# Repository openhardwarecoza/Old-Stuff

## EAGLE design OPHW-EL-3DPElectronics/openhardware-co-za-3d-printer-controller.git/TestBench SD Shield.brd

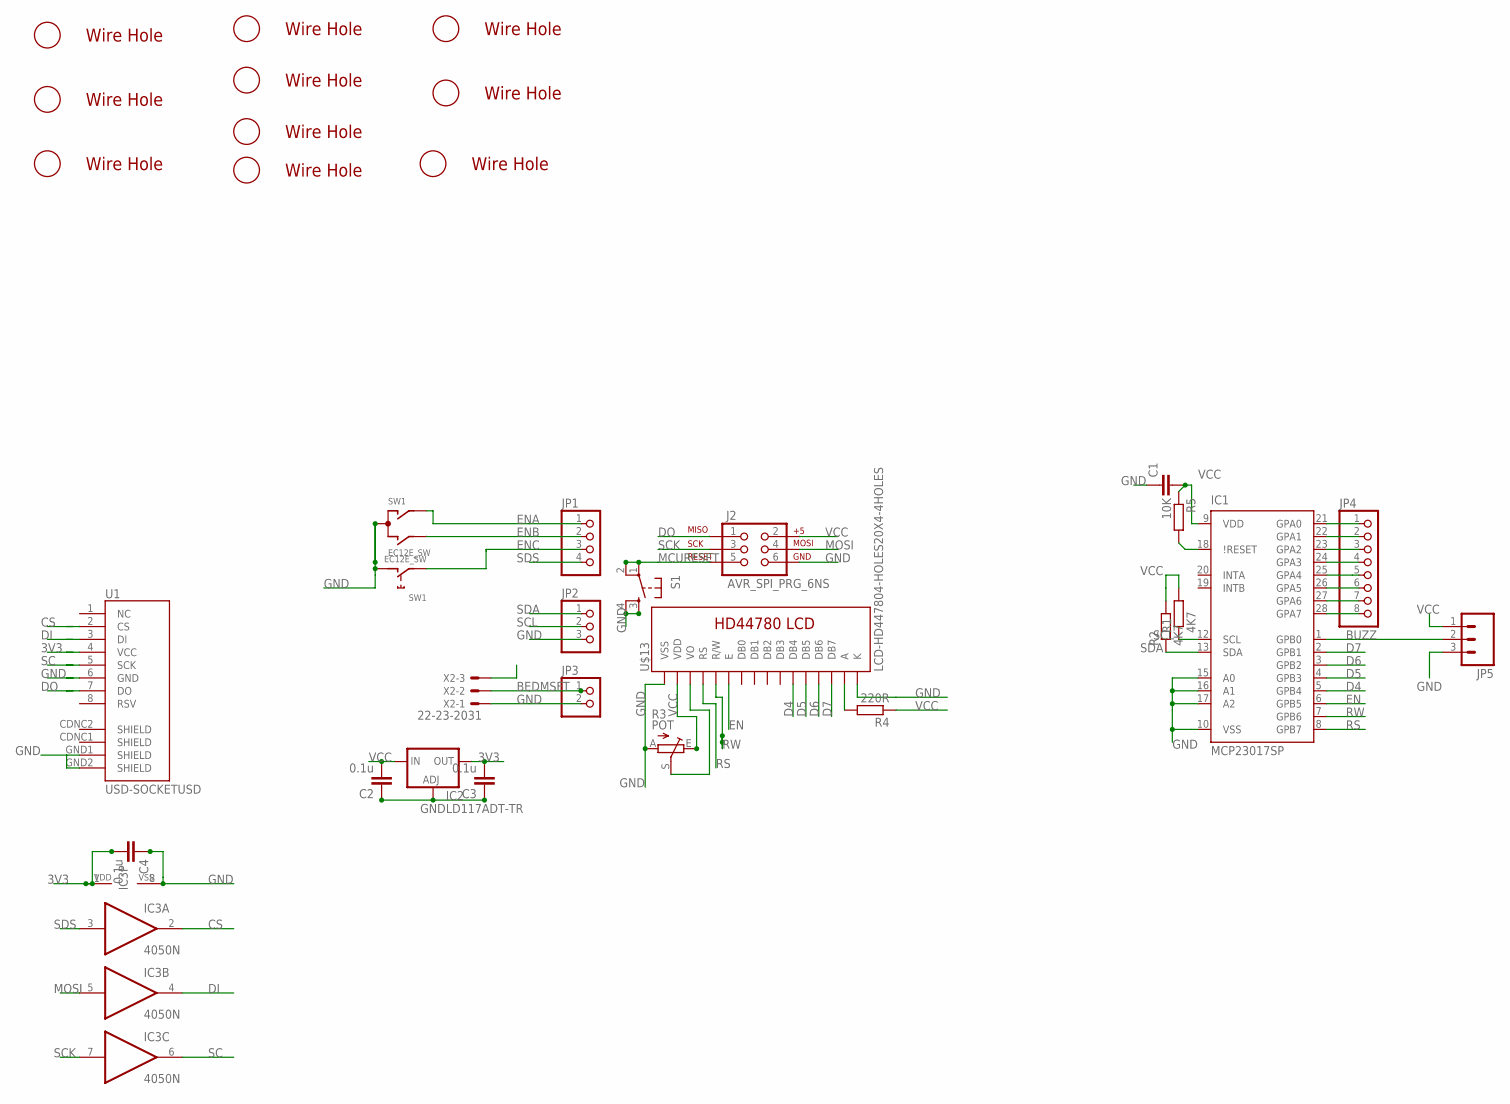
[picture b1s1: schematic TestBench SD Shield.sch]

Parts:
C1: CAPKIT; CAP-PTH-SMALL-KIT
C2, C3, C4: 0.1u; CAP-PTH-SMALL-KIT
IC1: MCP23017SP; DIL28-3
IC2: LD117ADT-TR; DPACK
IC3: 4050N; DIL16
J2: AVR_SPI_PRG_6NS; 2X3-NS
JP1: PINHD-1X4; 1X04
JP2: PINHD-1X3; 1X03
JP3: PINHD-1X2; 1X02
JP4: PINHD-1X8; 1X08
JP5: M03LONGPADS; 1X03_LONGPADS
R1, R2: 4K7; 0204/7
R3: POT; CA9V
R4: 220R; 0204/7
R5: 10K; 0204/7
S1: TAC_SWITCHPTH; TACTILE-PTH
SW1: EC12E_SW; ALPS_EC12E_SW
U1: USD-SOCKETUSD; USD-SOCKET-PP
U$1, U$3, U$5, U$6, U$7, U$8, U$9, U$10, U$11, U$12: 3MMHOLE
U$13: LCD-HD447804-HOLES20X4-4HOLES; LCD-20X4-4HOLES
X2: 22-23-2031

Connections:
3V3: C3.2, C4.2, IC2.4 (OUT), IC3.1 (VDD), U1.4 (VCC)
BEDMSFT: JP3.1, X2.2
BUZZ: IC1.1 (GPB0), JP5.2
CONTRAST: R3.S, U$13.P$3 (VO)
CS: IC3.2 (O), U1.2 (CS)
D4: IC1.5 (GPB4), U$13.P$11 (DB4)
D5: IC1.4 (GPB3), U$13.P$12 (DB5)
D6: IC1.3 (GPB2), U$13.P$13 (DB6)
D7: IC1.2 (GPB1), U$13.P$14 (DB7)
DI: IC3.4 (O), U1.3 (DI)
DO: J2.1, U1.7 (DO)
EN: IC1.6 (GPB5), U$13.P$6 (E)
ENA: JP1.1, SW1.A
ENB: JP1.2, SW1.B
ENC: JP1.3, SW1.E (2)
GND: C1.1, C2.1, C3.1, C4.1, IC1.10 (VSS), IC1.15 (A0), IC1.16 (A1), IC1.17 (A2), IC2.1 (ADJ), IC3.8 (VSS), J2.6, JP2.3, JP3.2, JP5.3, R3.A, S1.3, S1.4, SW1.C, SW1.D (1), U1.6 (GND), U1.GND1 (SHIELD), U1.GND2 (SHIELD), U$13.P$1 (VSS), U$13.P$16 (K), X2.1
MCURESET: J2.5, S1.1, S1.2
MOSI: IC3.5 (I), J2.4
unnamed: IC1.28 (GPA7), JP4.8
unnamed: IC1.27 (GPA6), JP4.7
unnamed: IC1.26 (GPA5), JP4.6
unnamed: IC1.25 (GPA4), JP4.5
unnamed: IC1.24 (GPA3), JP4.4
unnamed: IC1.23 (GPA2), JP4.3
unnamed: IC1.22 (GPA1), JP4.2
unnamed: IC1.21 (GPA0), JP4.1
unnamed: R4.2, U$13.P$15 (A)
unnamed: IC1.18 (\!RESET), R5.2
RS: IC1.8 (GPB7), U$13.P$4 (RS)
RW: IC1.7 (GPB6), U$13.P$5 (R/W)
SC: IC3.6 (O), U1.5 (SCK)
SCK: IC3.7 (I), J2.3
SCL: IC1.12 (SCL), JP2.2, R1.1
SDA: IC1.13 (SDA), JP2.1, R2.1
SDS: IC3.3 (I), JP1.4
VCC: C1.2, C2.2, IC1.9 (VDD), IC2.3 (IN), J2.2, JP5.1, R1.2, R2.2, R3.E, R4.1, R5.1, U$13.P$2 (VDD)

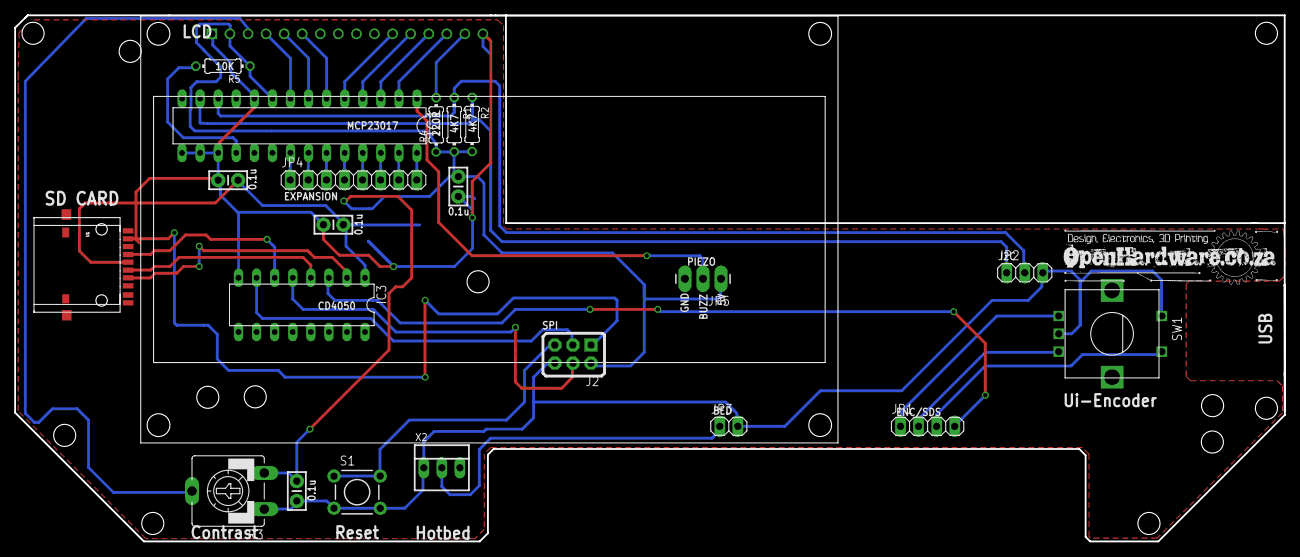
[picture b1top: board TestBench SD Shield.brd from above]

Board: 2 copper layers, 178.5 x 74.0 mm, 35 parts (1 on the bottom side), 36 nets.

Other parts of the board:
U$2, U$4: 3MMHOLE

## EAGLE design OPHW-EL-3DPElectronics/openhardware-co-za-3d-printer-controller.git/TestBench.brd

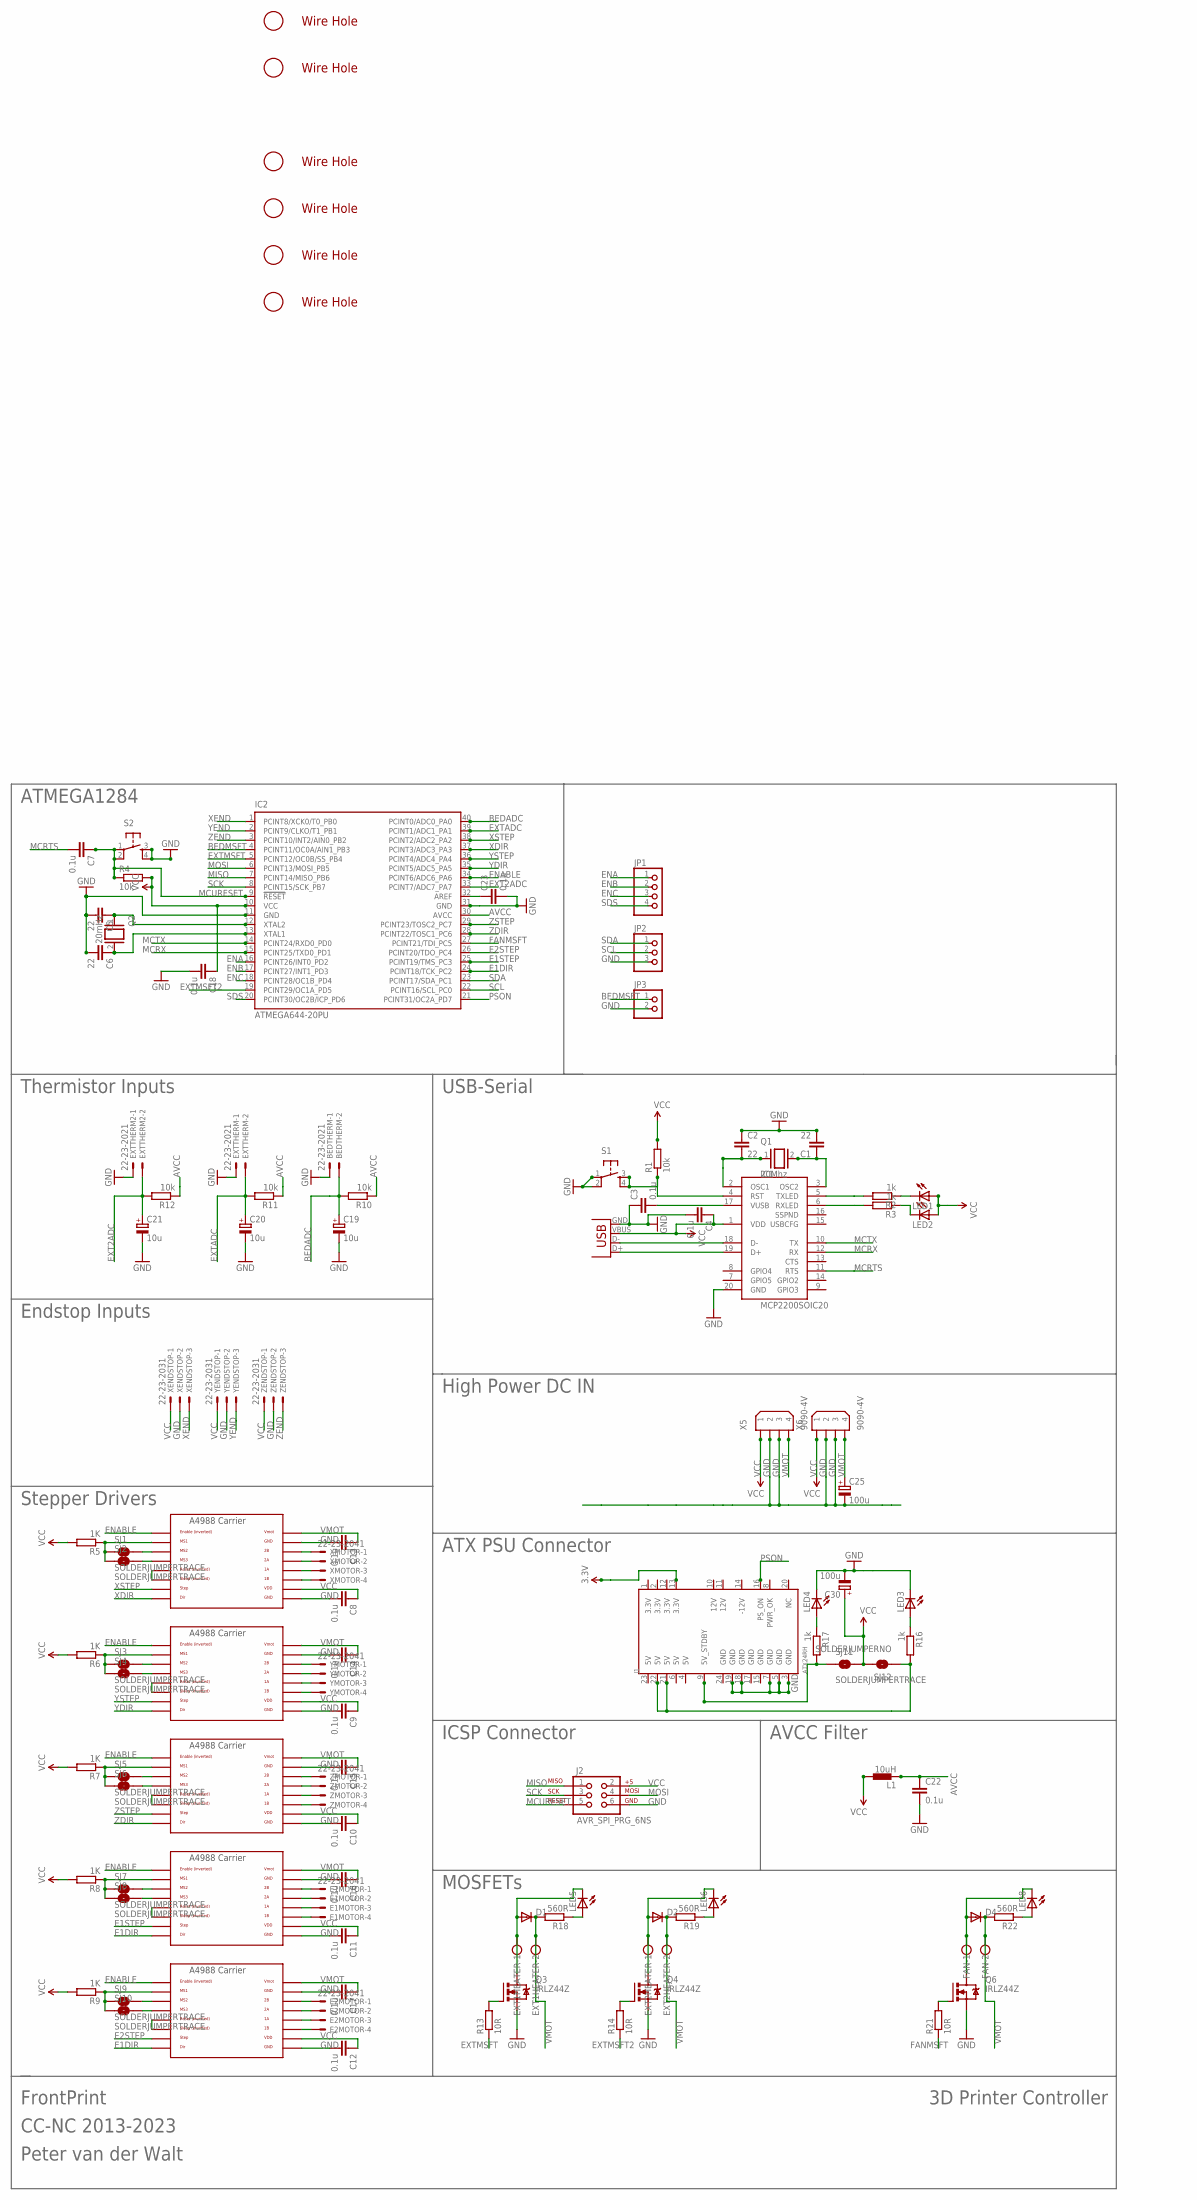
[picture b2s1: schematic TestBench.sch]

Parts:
BEDTHERM: 22-23-2021
C1, C2, C5, C6: 22; CAP-PTH-SMALL-KIT
C3, C4, C7, C8, C9, C10, C11, C12, C13, C14, C15, C16, C17, C18, C22, C23: 0.1u; CAP-PTH-SMALL-KIT
C19, C20, C21: 10u; E2,5-5
C25, C30: 100u; E5-8,5
D1, D2, D4: DIODE1N4148; DIODE-1N4148
E1MOTOR, E2MOTOR: 22-23-2041
EPOLOLU, EPOLOLU2: POLOLU_A4983CARRIER; A4988BREAKOUT
EXT1HEATER, EXT2HEATER: W237-102
EXTTHERM, EXTTHERM2: 22-23-2021
FAN: W237-102
IC1: MCP2200SOIC20; SOIC20
IC2: ATMEGA644-20PU; DIL40
J1: ATX24RH; ATX24_RIGHT_ANGLE
J2: AVR_SPI_PRG_6NS; 2X3-NS
JP1: PINHD-1X4; 1X04
JP2: PINHD-1X3; 1X03
JP3: PINHD-1X2; 1X02
L1: 10uH; BL01RN1A
LED1, LED2, LED3, LED4, LED5, LED6, LED8: LED3MM
Q1: 20Mhz; QS
Q2: 20mHz; QS
Q3, Q4, Q6: IRLZ44Z; TO220BH
R1, R4, R10, R11, R12: 10k; 0204/7
R2, R3, R16, R17: 1k; 0204/7
R5, R6, R7, R8, R9: 1K; 0204/7
R13, R14, R21: 10R; 0204/7
R18, R19, R22: 560R; 0204/7
S1, S2: TAC_SWITCHPTH; TACTILE-PTH
SJ1, SJ2, SJ3, SJ4, SJ5, SJ6, SJ7, SJ8, SJ9, SJ10, SJ11: SOLDERJUMPERTRACE; SJ_2S-TRACE
SJ12: SOLDERJUMPERNO; SJ_2S-NO
U$1, U$3, U$5, U$6, U$7, U$8: 3MMHOLE
X1: USBPTH; USB-B-PTH
X5, X6: 9090-4V
XENDSTOP: 22-23-2031
XMOTOR: 22-23-2041
XPOLOLU: POLOLU_A4983CARRIER; A4988BREAKOUT
YENDSTOP: 22-23-2031
YMOTOR: 22-23-2041
YPOLOLU: POLOLU_A4983CARRIER; A4988BREAKOUT
ZENDSTOP: 22-23-2031
ZMOTOR: 22-23-2041
ZPOLOLU: POLOLU_A4983CARRIER; A4988BREAKOUT

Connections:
3.3V: J1.13 (3.3V)
AVCC: C22.1, IC2.30 (AVCC), L1.1, R10.1, R11.1, R12.1
BEDADC: BEDTHERM.2, C19.+, IC2.40 (PCINT0/ADC0_PA0), R10.2
BEDMSFT: IC2.4 (PCINT11/OC0A/AIN1_PB3), JP3.1
E1DIR: EPOLOLU.DIR, EPOLOLU2.DIR, IC2.24 (PCINT18/TCK_PC2)
E1STEP: EPOLOLU.STEP, IC2.25 (PCINT19/TMS_PC3)
E2STEP: EPOLOLU2.STEP, IC2.26 (PCINT20/TDO_PC4)
ENA: IC2.16 (PCINT26/INT0_PD2), JP1.1
ENABLE: EPOLOLU.EN, EPOLOLU2.EN, IC2.34 (PCINT6/ADC6_PA6), XPOLOLU.EN, YPOLOLU.EN, ZPOLOLU.EN
ENB: IC2.17 (PCINT27/INT1_PD3), JP1.2
ENC: IC2.18 (PCINT28/OC1B_PD4), JP1.3
EXT2ADC: C21.+, EXTTHERM2.2, IC2.33 (PCINT7/ADC7_PA7), R12.2
EXTADC: C20.+, EXTTHERM.2, IC2.39 (PCINT1/ADC1_PA1), R11.2
EXTMSFT: IC2.5 (PCINT12/OC0B/SS_PB4), R13.1
EXTMSFT2: IC2.19 (PCINT29/OC1A_PD5), R14.1
FANMSFT: IC2.27 (PCINT21/TDI_PC5), R21.1
GND: BEDTHERM.1, C1.2, C2.1, C3.1, C4.2, C5.2, C6.2, C8.2, C9.2, C10.2, C11.2, C12.2, C13.2, C14.2, C15.2, C16.2, C17.2, C18.2, C19.-, C20.-, C21.-, C22.2, C23.2, C25.-, C30.-, EPOLOLU.GND, EPOLOLU.GND@0 (GND), EPOLOLU2.GND, EPOLOLU2.GND@0 (GND), EXTTHERM.1, EXTTHERM2.1, IC1.20 (GND), IC2.11 (GND), IC2.31 (GND), J1.3 (GND), J1.5 (GND), J1.7 (GND), J1.18 (GND), J1.19 (GND), J2.6, JP2.3, JP3.2, LED3.K (C), LED4.K (C), Q3.S, Q4.S, Q6.S, S1.1, S1.2, S2.3, S2.4, X1.GND, X5.2, X5.3, X6.2, X6.3, XENDSTOP.2, XPOLOLU.GND, XPOLOLU.GND@0 (GND), YENDSTOP.2, YPOLOLU.GND, YPOLOLU.GND@0 (GND), ZENDSTOP.2, ZPOLOLU.GND, ZPOLOLU.GND@0 (GND)
MCRTS: C7.2, IC1.11 (RTS)
MCRX: IC1.12 (RX), IC2.15 (PCINT25/TXD0_PD1)
MCTX: IC1.10 (TX), IC2.14 (PCINT24/RXD0_PD0)
MCURESET: C7.1, IC2.9 (!RESET), J2.5, R4.1, S2.1, S2.2
MISO: IC2.7 (PCINT14/MISO_PB6), J2.1
MOSI: IC2.6 (PCINT13/MOSI_PB5), J2.4
unnamed: C2.2, IC1.2 (OSC1), Q1.1
unnamed: C1.1, IC1.3 (OSC2), Q1.2
unnamed: IC1.5 (TXLED), R2.2
unnamed: IC1.18 (D-), X1.D-
unnamed: IC1.19 (D+), X1.D+
unnamed: IC1.6 (RXLED), R3.2
unnamed: C3.2, IC1.17 (VUSB)
unnamed: Q3.G, R13.2
unnamed: LED1.K (C), R2.1
unnamed: LED2.K (C), R3.1
unnamed: C5.1, IC2.12 (XTAL2), Q2.1
unnamed: C6.1, IC2.13 (XTAL1), Q2.2
unnamed: IC1.4 (RST), R1.1, S1.3, S1.4
unnamed: R7.1, SJ5.1, SJ6.1, ZPOLOLU.MS1
unnamed: SJ6.2, ZPOLOLU.MS3
unnamed: SJ5.2, ZPOLOLU.MS2
unnamed: EPOLOLU.MS2, SJ7.2
unnamed: EPOLOLU.MS3, SJ8.2
unnamed: EPOLOLU.MS1, R8.1, SJ7.1, SJ8.1
unnamed: SJ3.2, YPOLOLU.MS2
unnamed: SJ4.2, YPOLOLU.MS3
unnamed: R6.1, SJ3.1, SJ4.1, YPOLOLU.MS1
unnamed: SJ1.2, XPOLOLU.MS2
unnamed: SJ2.2, XPOLOLU.MS3
unnamed: R5.1, SJ1.1, SJ2.1, XPOLOLU.MS1
unnamed: XPOLOLU.RST, XPOLOLU.SLP (SLEEP)
unnamed: YPOLOLU.RST, YPOLOLU.SLP (SLEEP)
unnamed: ZPOLOLU.RST, ZPOLOLU.SLP (SLEEP)
unnamed: EPOLOLU.RST, EPOLOLU.SLP (SLEEP)
unnamed: E1MOTOR.1, EPOLOLU.2B
unnamed: E1MOTOR.2, EPOLOLU.2A
unnamed: E1MOTOR.3, EPOLOLU.1A
unnamed: E1MOTOR.4, EPOLOLU.1B
unnamed: ZMOTOR.4, ZPOLOLU.1B
unnamed: ZMOTOR.3, ZPOLOLU.1A
unnamed: ZMOTOR.2, ZPOLOLU.2A
unnamed: ZMOTOR.1, ZPOLOLU.2B
unnamed: YMOTOR.4, YPOLOLU.1B
unnamed: YMOTOR.3, YPOLOLU.1A
unnamed: YMOTOR.2, YPOLOLU.2A
unnamed: YMOTOR.1, YPOLOLU.2B
unnamed: XMOTOR.4, XPOLOLU.1B
unnamed: XMOTOR.3, XPOLOLU.1A
unnamed: XMOTOR.2, XPOLOLU.2A
unnamed: XMOTOR.1, XPOLOLU.2B
unnamed: EPOLOLU2.MS2, SJ9.2
unnamed: EPOLOLU2.MS3, SJ10.2
unnamed: EPOLOLU2.MS1, R9.1, SJ9.1, SJ10.1
unnamed: EPOLOLU2.RST, EPOLOLU2.SLP (SLEEP)
unnamed: E2MOTOR.1, EPOLOLU2.2B
unnamed: E2MOTOR.2, EPOLOLU2.2A
unnamed: E2MOTOR.3, EPOLOLU2.1A
unnamed: E2MOTOR.4, EPOLOLU2.1B
unnamed: C23.1, IC2.32 (AREF)
unnamed: D1.A, EXT1HEATER.1, LED5.K (C), Q3.D
unnamed: Q4.G, R14.2
unnamed: D2.A, EXT2HEATER.1, LED6.K (C), Q4.D
unnamed: J1.21 (5V), J1.22 (5V), R16.2, SJ12.1
unnamed: LED5.A, R18.1
unnamed: J1.9 (5V_STDBY), R17.2, SJ11.1
unnamed: LED4.A, R17.1
unnamed: LED3.A, R16.1
unnamed: Q6.G, R21.2
unnamed: LED6.A, R19.1
unnamed: D4.A, FAN.1, LED8.K (C), Q6.D
unnamed: LED8.A, R22.1
PSON: IC2.21 (PCINT31/OC2A_PD7), J1.16 (PS_ON)
SCK: IC2.8 (PCINT15/SCK_PB7), J2.3
SCL: IC2.22 (PCINT16/SCL_PC0), JP2.2
SDA: IC2.23 (PCINT17/SDA_PC1), JP2.1
SDS: IC2.20 (PCINT30/OC2B/ICP_PD6), JP1.4
VCC: C4.1, C8.1, C9.1, C10.1, C11.1, C12.1, C18.1, C30.+, EPOLOLU.VDD, EPOLOLU2.VDD, IC1.1 (VDD), IC2.10 (VCC), J2.2, L1.2, LED1.A, LED2.A, R1.2, R4.2, R5.2, R6.2, R7.2, R8.2, R9.2, SJ11.2, SJ12.2, X1.VBUS, X5.1, X6.1, XENDSTOP.1, XPOLOLU.VDD, YENDSTOP.1, YPOLOLU.VDD, ZENDSTOP.1, ZPOLOLU.VDD
VMOT: C13.1, C14.1, C15.1, C16.1, C17.1, C25.+, D1.C, D2.C, D4.C, EPOLOLU.VMOT, EPOLOLU2.VMOT, EXT1HEATER.2, EXT2HEATER.2, FAN.2, R18.2, R19.2, R22.2, X5.4, X6.4, XPOLOLU.VMOT, YPOLOLU.VMOT, ZPOLOLU.VMOT
XDIR: IC2.37 (PCINT3/ADC3_PA3), XPOLOLU.DIR
XEND: IC2.1 (PCINT8/XCK0/T0_PB0), XENDSTOP.3
XSTEP: IC2.38 (PCINT2/ADC2_PA2), XPOLOLU.STEP
YDIR: IC2.35 (PCINT5/ADC5_PA5), YPOLOLU.DIR
YEND: IC2.2 (PCINT9/CLKO/T1_PB1), YENDSTOP.3
YSTEP: IC2.36 (PCINT4/ADC4_PA4), YPOLOLU.STEP
ZDIR: IC2.28 (PCINT22/TOSC1_PC6), ZPOLOLU.DIR
ZEND: IC2.3 (PCINT10/INT2/AIN0_PB2), ZENDSTOP.3
ZSTEP: IC2.29 (PCINT23/TOSC2_PC7), ZPOLOLU.STEP

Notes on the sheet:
Thermistor Inputs
Endstop Inputs
Stepper Drivers
USB-Serial
AVCC Filter
ATX PSU Connector
ICSP Connector
MOSFETs
High Power DC IN
ATMEGA1284
FrontPrint
CC-NC 2013-2023
Peter van der Walt
3D Printer Controller

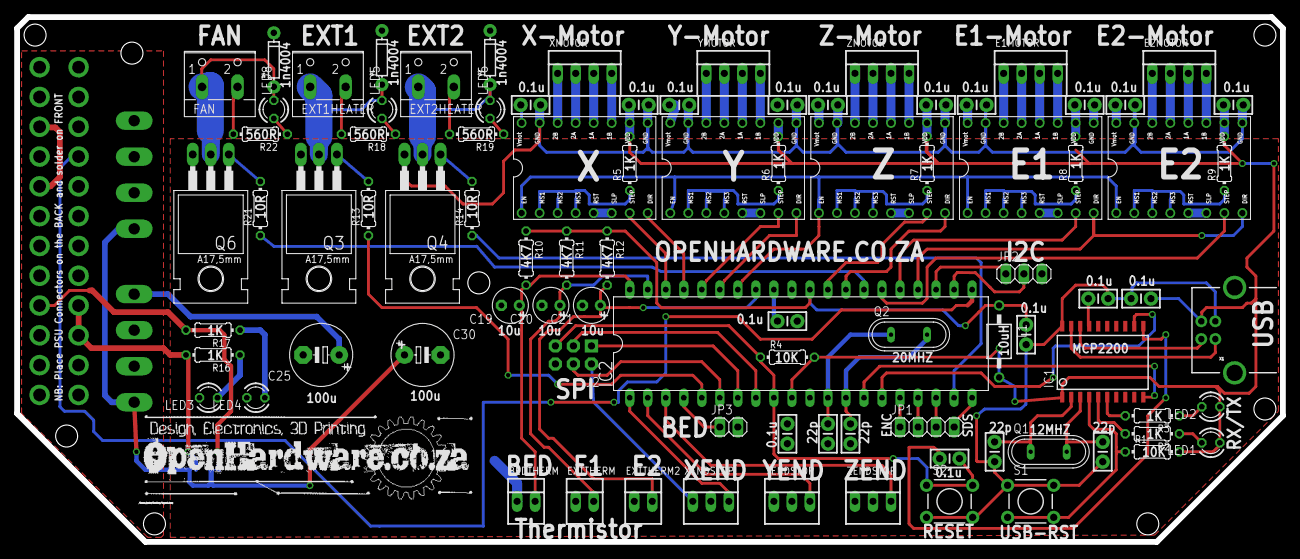
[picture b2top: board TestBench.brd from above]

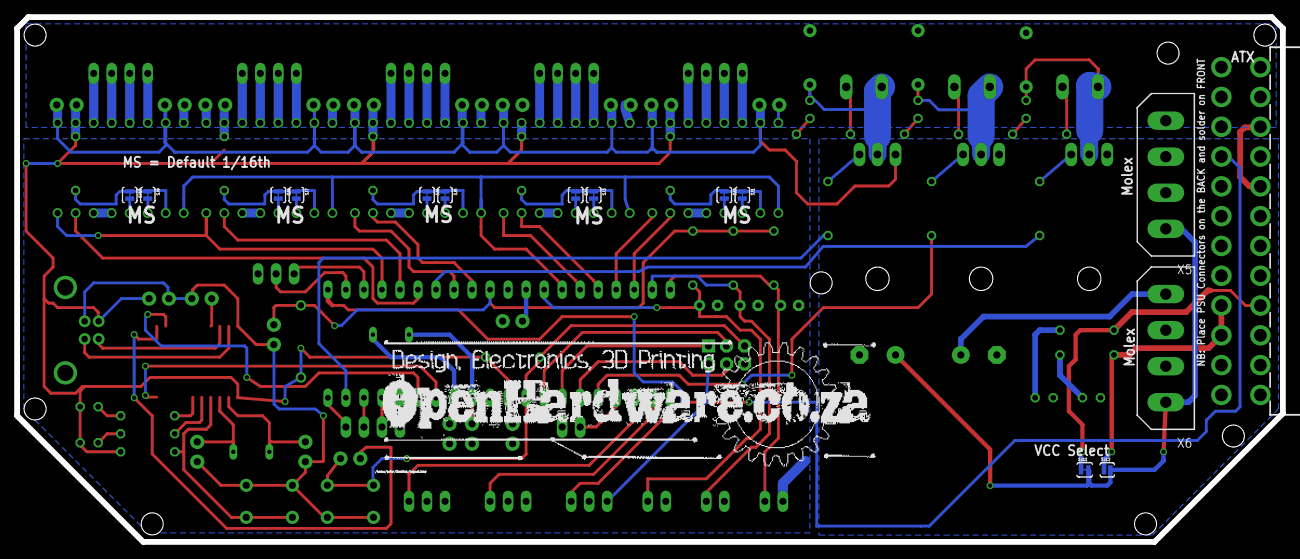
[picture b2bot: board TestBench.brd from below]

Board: 2 copper layers, 178.4 x 74.0 mm, 112 parts (15 on the bottom side), 104 nets.

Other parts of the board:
U$2, U$4: 3MMHOLE

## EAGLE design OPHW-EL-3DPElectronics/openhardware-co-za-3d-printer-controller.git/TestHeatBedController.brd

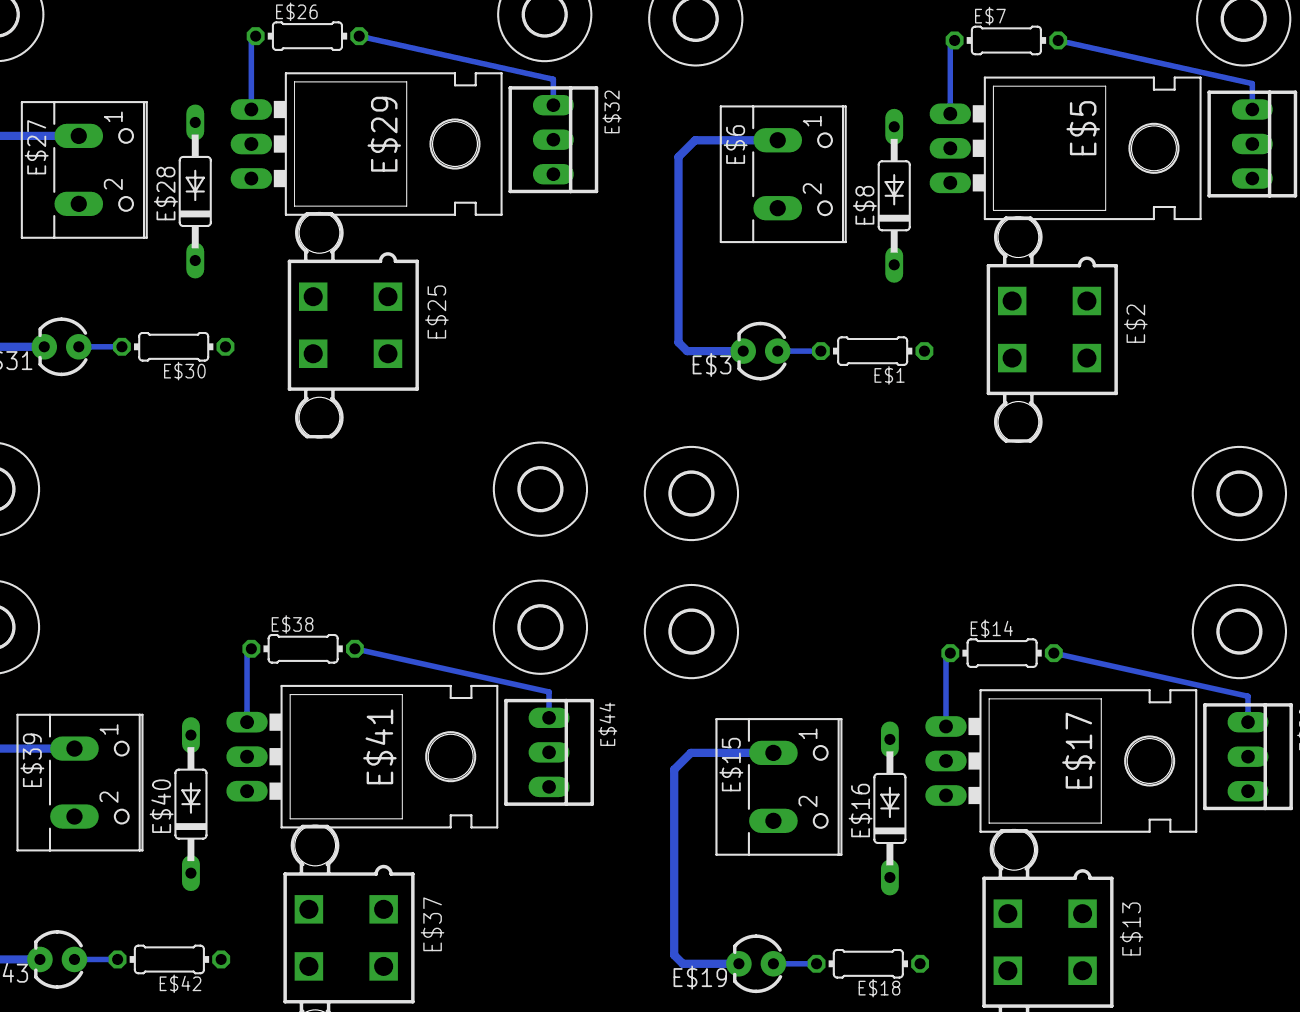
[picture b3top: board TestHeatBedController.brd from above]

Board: 2 copper layers, 48 parts (0 on the bottom side), 24 nets.

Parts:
E$1, E$7, E$14, E$18, E$26, E$30, E$38, E$42: 0204/7
E$2, E$13, E$25, E$37: 5566-4
E$3, E$19, E$31, E$43: LED3MM
E$4, E$20, E$32, E$44: 22-23-2031
E$5, E$17, E$29, E$41: TO-220-ALT
E$6, E$15, E$27, E$39: W237-102
E$8, E$16, E$28, E$40: C2992
E$9, E$10, E$11, E$12, E$21, E$22, E$23, E$24, E$33, E$34, E$35, E$36, E$45, E$46, E$47, E$48: 3,0

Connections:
12V: E$1.1, E$2.3, E$2.4, E$6.2, E$8.C
12V1: E$13.3, E$13.4, E$15.2, E$16.C, E$18.1
12V2: E$25.3, E$25.4, E$27.2, E$28.C, E$30.1
12V3: E$37.3, E$37.4, E$39.2, E$40.C, E$42.1
GATE: E$5.IN, E$7.1
GATE1: E$14.1, E$17.IN
GATE2: E$26.1, E$29.IN
GATE3: E$38.1, E$41.IN
GND: E$2.1, E$2.2, E$4.3, E$5.OUT
GND1: E$13.1, E$13.2, E$17.OUT, E$20.3
GND2: E$25.1, E$25.2, E$29.OUT, E$32.3
GND3: E$37.1, E$37.2, E$41.OUT, E$44.3
S$1: E$18.2, E$19.A
S$2: E$1.2, E$3.A
S$3: E$30.2, E$31.A
S$4: E$42.2, E$43.A
SIG: E$4.1, E$7.2
SIG1: E$14.2, E$20.1
SIG2: E$26.2, E$32.1
SIG3: E$38.2, E$44.1
VMOS: E$3.K, E$4.2, E$5.GND, E$6.1, E$8.A
VMOS1: E$15.1, E$16.A, E$17.GND, E$19.K, E$20.2
VMOS2: E$27.1, E$28.A, E$29.GND, E$31.K, E$32.2
VMOS3: E$39.1, E$40.A, E$41.GND, E$43.K, E$44.2

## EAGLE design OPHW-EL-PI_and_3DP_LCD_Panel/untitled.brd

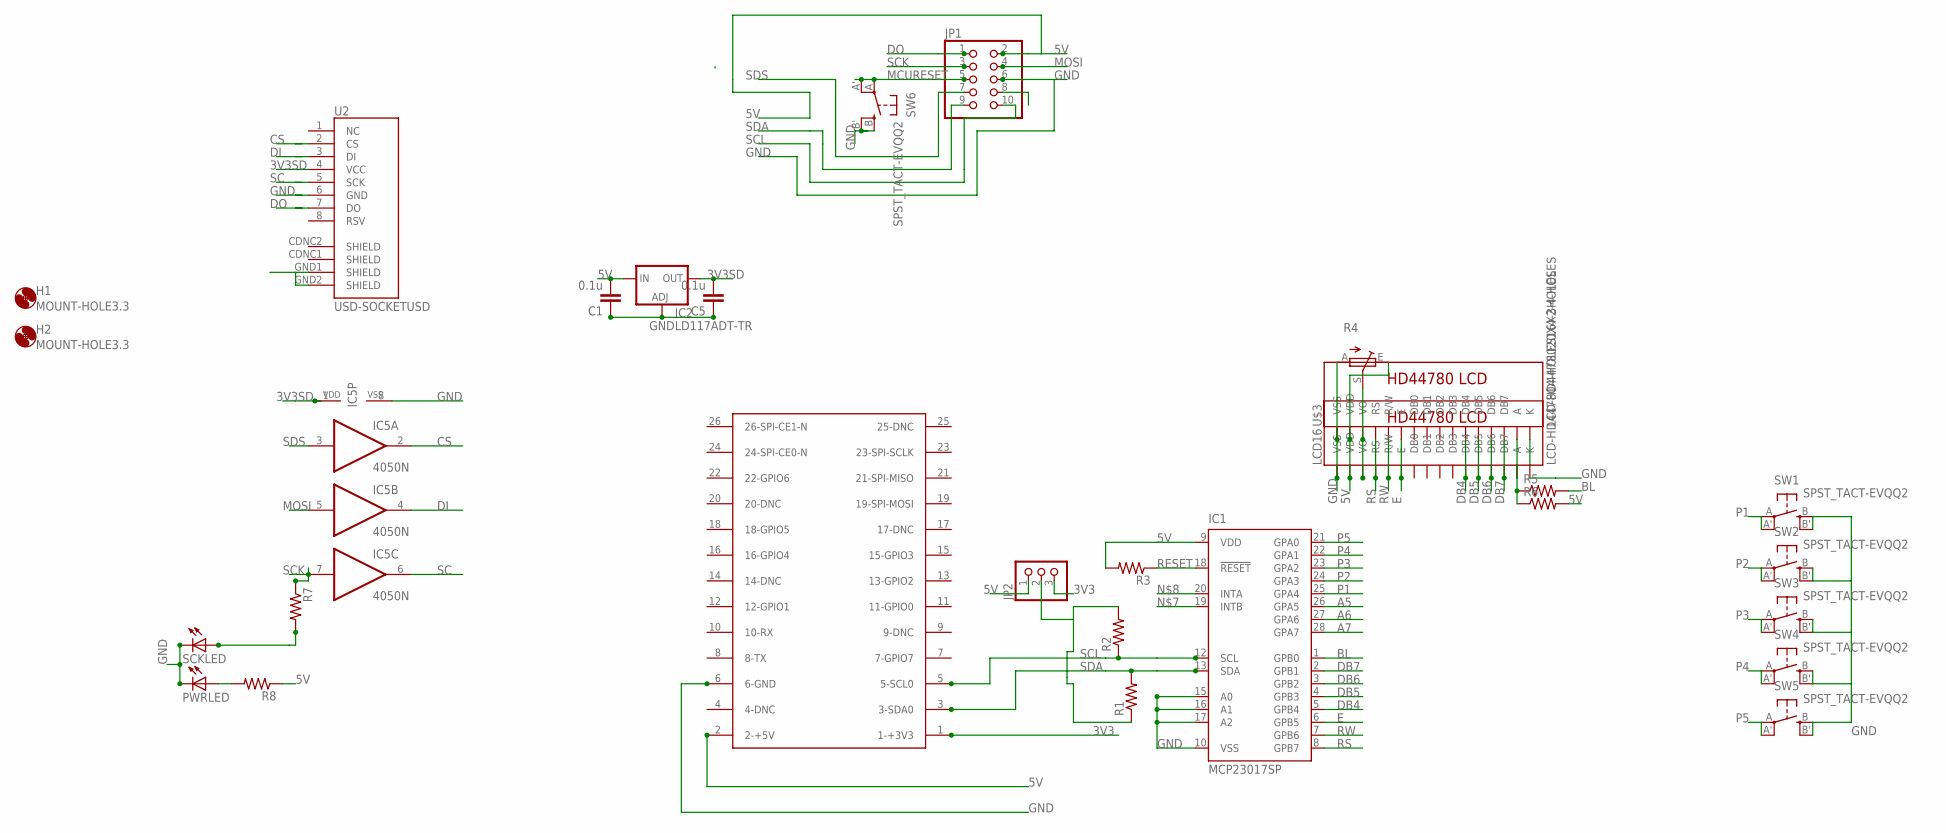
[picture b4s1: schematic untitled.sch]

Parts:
C1, C5: 0.1u; CAP-PTH-SMALL-KIT
H1, H2: MOUNT-HOLE3.3; 3,3
IC1: MCP23017SP; DIL28-3
IC2: LD117ADT-TR; DPACK
IC5: 4050N; DIL16
JP1: PINHD-2X5; 2X05
JP2: PINHD-1X3; 1X03
LCD16: LCD-HD447804-HOLES16X2-4-HOLES; LCD-16X2-4HOLES
PWRLED: LED1206; LED-1206
R1, R2, R3, R5, R6, R7, R8: R-US_0204/7; 0204/7
R4: TRIM_EU-CA6V; CA6V
SCKLED: LED1206; LED-1206
SW1, SW2, SW3, SW4, SW5, SW6: SPST_TACT-EVQQ2; EVQ-Q2
U2: USD-SOCKETUSD; USD-SOCKET-PP
U$2: RASPBERRY-PI
U$3: LCD-HD4478020X4-3HOLES; LCD-20X4-3HOLES

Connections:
3V3: JP2.3, U$2.1 (1-+3V3)
3V3SD: C5.2, IC2.4 (OUT), IC5.1 (VDD), U2.4 (VCC)
5V: C1.2, IC1.9 (VDD), IC2.3 (IN), JP1.2, JP2.1, LCD16.2 (VDD), R3.2, R4.E, R6.2, R8.1, U$2.2 (2-+5V), U$3.P$2 (VDD)
A5: IC1.26 (GPA5)
A6: IC1.27 (GPA6)
A7: IC1.28 (GPA7)
BL: IC1.1 (GPB0), R5.2
CS: IC5.2 (O), U2.2 (CS)
DB4: IC1.5 (GPB4), LCD16.11 (DB4), U$3.P$11 (DB4)
DB5: IC1.4 (GPB3), LCD16.12 (DB5), U$3.P$12 (DB5)
DB6: IC1.3 (GPB2), LCD16.13 (DB6), U$3.P$13 (DB6)
DB7: IC1.2 (GPB1), LCD16.14 (DB7), U$3.P$14 (DB7)
DI: IC5.4 (O), U2.3 (DI)
DO: JP1.1, U2.7 (DO)
E: IC1.6 (GPB5), LCD16.6 (E), U$3.P$6 (E)
GND: C1.1, C5.1, IC1.10 (VSS), IC1.15 (A0), IC1.16 (A1), IC1.17 (A2), IC2.1 (ADJ), IC5.8 (VSS), JP1.6, LCD16.1 (VSS), LCD16.16 (K), PWRLED.C, R4.A, SCKLED.C, SW1.B (S), SW1.B' (S1), SW2.B (S), SW2.B' (S1), SW3.B (S), SW3.B' (S1), SW4.B (S), SW4.B' (S1), SW5.B (S), SW5.B' (S1), SW6.B (S), SW6.B' (S1), U2.6 (GND), U2.GND1 (SHIELD), U2.GND2 (SHIELD), U$2.6 (6-GND), U$3.P$1 (VSS)
I2CPULL: JP2.2, R1.1, R2.2
MCURESET: JP1.5, SW6.A, SW6.A' (P1)
MOSI: IC5.5 (I), JP1.4
unnamed: LCD16.3 (VO), R4.S, U$3.P$3 (VO)
unnamed: LCD16.15 (A), R5.1, R6.1, U$3.P$15 (A)
unnamed: PWRLED.A, R8.2
unnamed: R7.2, SCKLED.A
P1: IC1.25 (GPA4), SW1.A, SW1.A' (P1)
P2: IC1.24 (GPA3), SW2.A, SW2.A' (P1)
P3: IC1.23 (GPA2), SW3.A, SW3.A' (P1)
P4: IC1.22 (GPA1), SW4.A, SW4.A' (P1)
P5: IC1.21 (GPA0), SW5.A, SW5.A' (P1)
RESET: IC1.18 (!RESET), R3.1
RS: IC1.8 (GPB7), LCD16.4 (RS), U$3.P$4 (RS)
RW: IC1.7 (GPB6), LCD16.5 (R/W), U$3.P$5 (R/W)
SC: IC5.6 (O), U2.5 (SCK)
SCK: IC5.7 (I), JP1.3, R7.1
SCL: IC1.12 (SCL), JP1.10, R2.1, U$2.5 (5-SCL0)
SDA: IC1.13 (SDA), JP1.9, R1.2, U$2.3 (3-SDA0)
SDS: IC5.3 (I), JP1.7

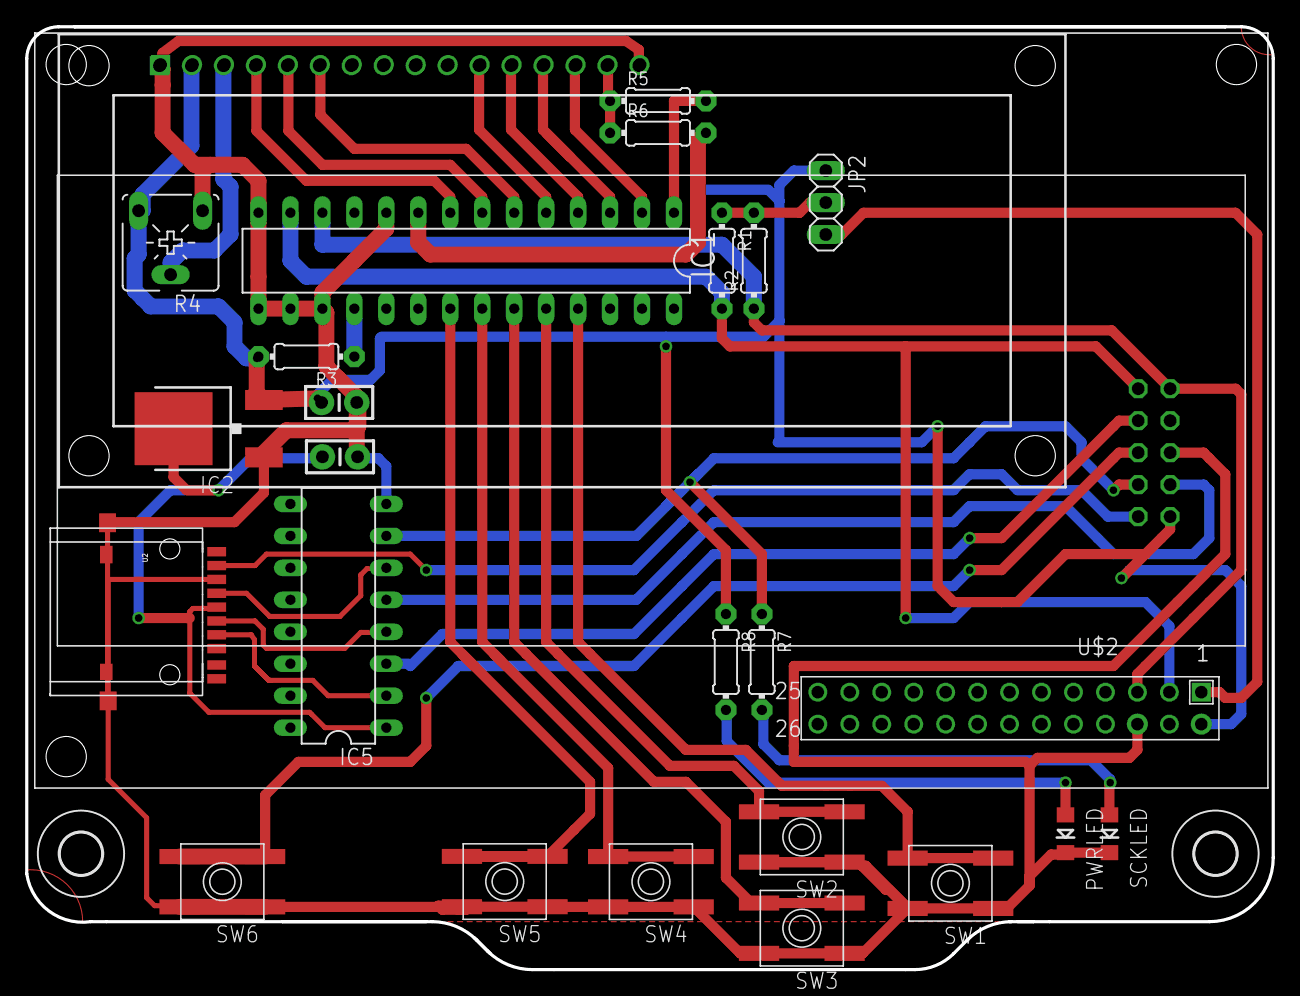
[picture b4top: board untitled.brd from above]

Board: 2 copper layers, 99.1 x 74.9 mm, 29 parts (1 on the bottom side), 33 nets.

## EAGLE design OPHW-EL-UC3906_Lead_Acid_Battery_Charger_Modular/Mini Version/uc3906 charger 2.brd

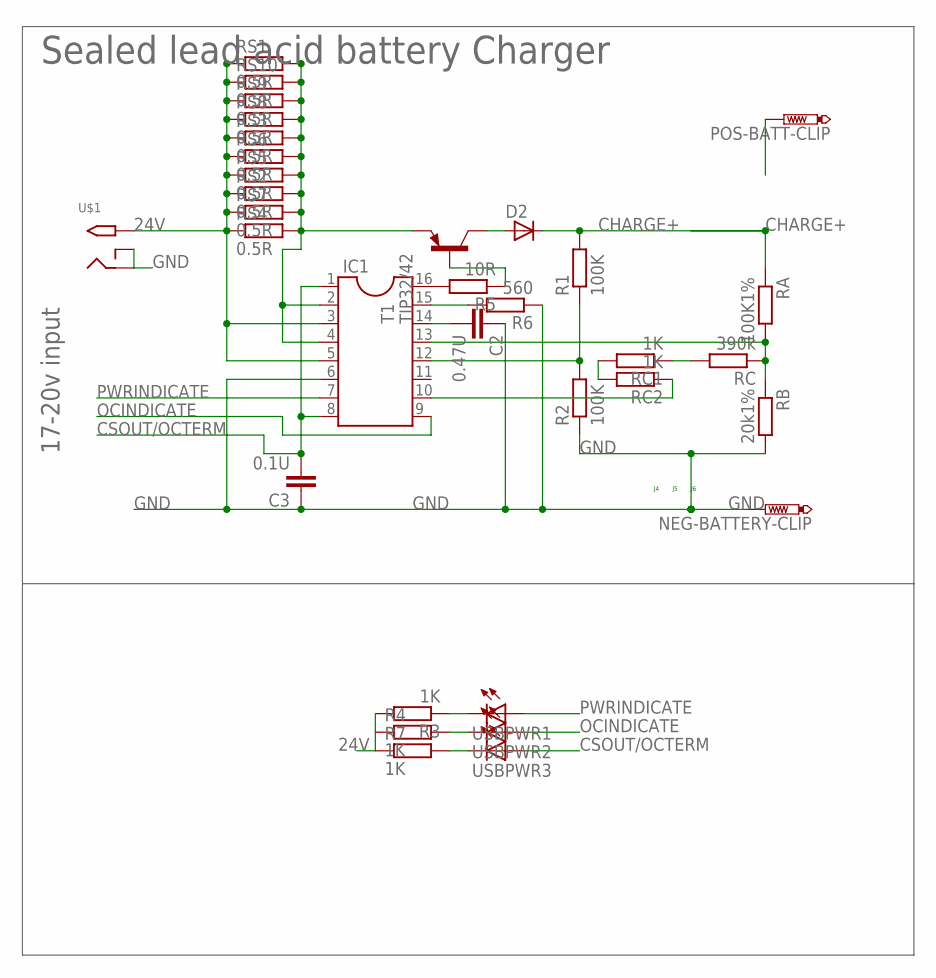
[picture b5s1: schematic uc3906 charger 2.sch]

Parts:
C2: 0.47U; C1206
C3: 0.1U; C1206
D2: D-MLL-41; MELF-MLL41
IC1: DIL16
NEG-BATTERY-CLIP: PTR1PAD1-20Y; P1-20Y
POS-BATT-CLIP: PTR1PAD1-20Y; P1-20Y
R1, R2: 100K; M1206
R3, R4, R7: 1K; M1206
R5: 10R; M1206
R6: 560; M1206
RA: 100K1%; M1206
RB: 20k1%; M1206
RC: 390k; M1206
RC1, RC2: 1K; M1206
RS1, RS3, RS5, RS7, RS9, RS10: 0.5R; R2512
RS2, RS4, RS6, RS8: 0.5R; 0617V
T1: TIP32/42; TO220
U$1: 2.1MMJACKTHM; PJ-102A
USBPWR1, USBPWR2, USBPWR3: LEDCHIPLED_1206; CHIPLED_1206

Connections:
24V: IC1.3, IC1.5, R3.2, R4.1, R7.1, RS1.1, RS2.1, RS3.1, RS4.1, RS5.1, RS6.1, RS7.1, RS8.1, RS9.1, RS10.1, U$1.TIP
CHARGE+: D2.1 (C), POS-BATT-CLIP.TP, R1.2, RA.1
CHARGEENABLE: IC1.12, R1.1, R2.2
COMPENSATION: C2.2, IC1.14
CSOUT/OCTERM: C3.2, IC1.1, IC1.8, USBPWR3.A
DRIVERSINK: IC1.16, R5.2
DRIVERSOURCE: IC1.15, R6.2
GND: C2.1, C3.1, IC1.6, NEG-BATTERY-CLIP.TP, R2.1, R6.1, RB.2, U$1.RING, U$1.RING_SW
IOUT: IC1.2, IC1.4, RS1.2, RS2.2, RS3.2, RS4.2, RS5.2, RS6.2, RS7.2, RS8.2, RS9.2, RS10.2, T1.3 (E)
unnamed: RC.2, RC1.1
unnamed: R3.1, USBPWR1.C
unnamed: RC1.2, RC2.2
unnamed: R4.2, USBPWR2.C
unnamed: R7.2, USBPWR3.C
unnamed: R5.1, T1.1 (B)
unnamed: D2.2 (A), T1.2 (C)
OCINDICATE: IC1.9, USBPWR2.A
PWRINDICATE: IC1.7, USBPWR1.A
STATELEVELCONTROL: IC1.10, RC2.1
VSENSE: IC1.13, RA.2, RB.1, RC.1

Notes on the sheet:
Sealed lead acid battery Charger
17-20v input

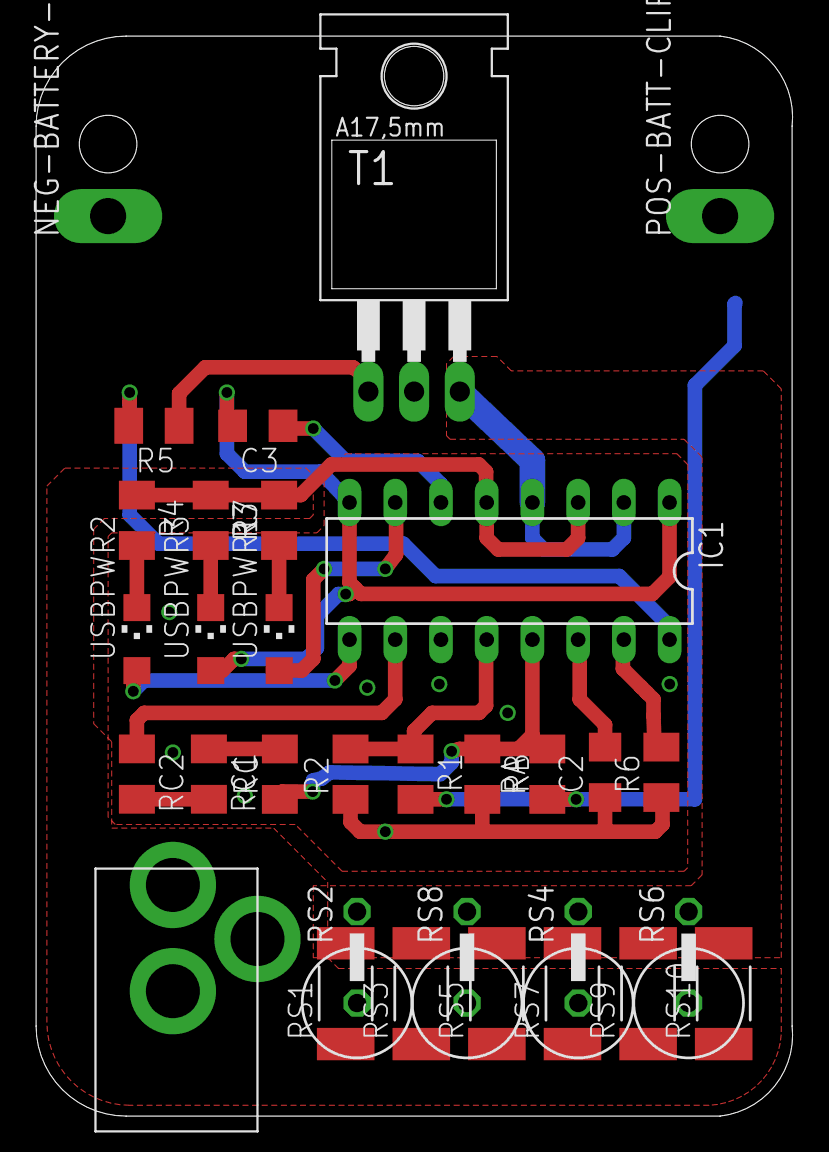
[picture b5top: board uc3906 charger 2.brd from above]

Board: 2 copper layers, 42.0 x 60.0 mm, 33 parts (1 on the bottom side), 20 nets.

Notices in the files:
OPHW-EL-PI_and_3DP_LCD_Panel/untitled.brd:
Licenced:  CC-BY-NC
(C) 2014
parts and their libraries:
SparkFun-Connectors: Licensing: CC v3.0 Share-Alike You are welcome to use this library for commercial purposes.
